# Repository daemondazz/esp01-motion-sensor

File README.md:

# ESP-01 Based Motion Sensor

This project is a very simple motion sensor using an ESP-01 ESP8266 module and
HC-SR501/DSN-FIR800 motion sensor.

Countless other designs using the same ESP module and motion sensor exist, this
project was created as a learning exercise. And because I wanted to.

## PCB

The PCB folder contains a Kicad project for a simple PCB that both the ESP
module and motion sensor are mounted to. It has the following features:

* Allows direct mounting of the ESP-01 module
* Allows direct mounting of the HC-SR501 sensor as a daughter board
* Uses a micro-USB connector for power input
* Contains a 3.3V regulator for powering the ESP-01
* Includes required pull-up resistors to allow the ESP-01 to boot reliably and
  then use the GPIO2 pin for the sensor input

## Software

The Software folder contains the Arduino sketch that I am running on my modules. 
It has the following features:

* Automatically publishes state changes into an MQTT topic based on the Chip ID 
  number embedded in the ESP-01
* Automatically publishes a name/version/OTA state message into an MQTT topic
  based on the Chip ID embedded into the ESP-01 every 10s as a keepalive
* Supports password authenticated OTA updates for the first 2 minutes after 
  powering on or being reset
* Uses the TX LED as an activity indicator

## TODO

* Create a 3D printed case to house the PCB
* Allow creation of a command MQTT topic to issue commands

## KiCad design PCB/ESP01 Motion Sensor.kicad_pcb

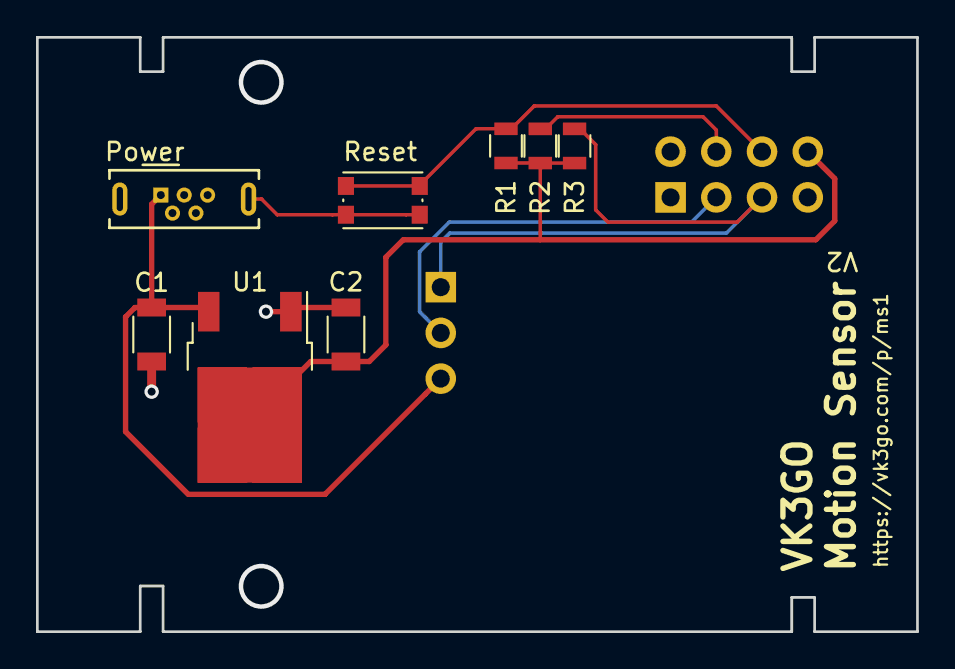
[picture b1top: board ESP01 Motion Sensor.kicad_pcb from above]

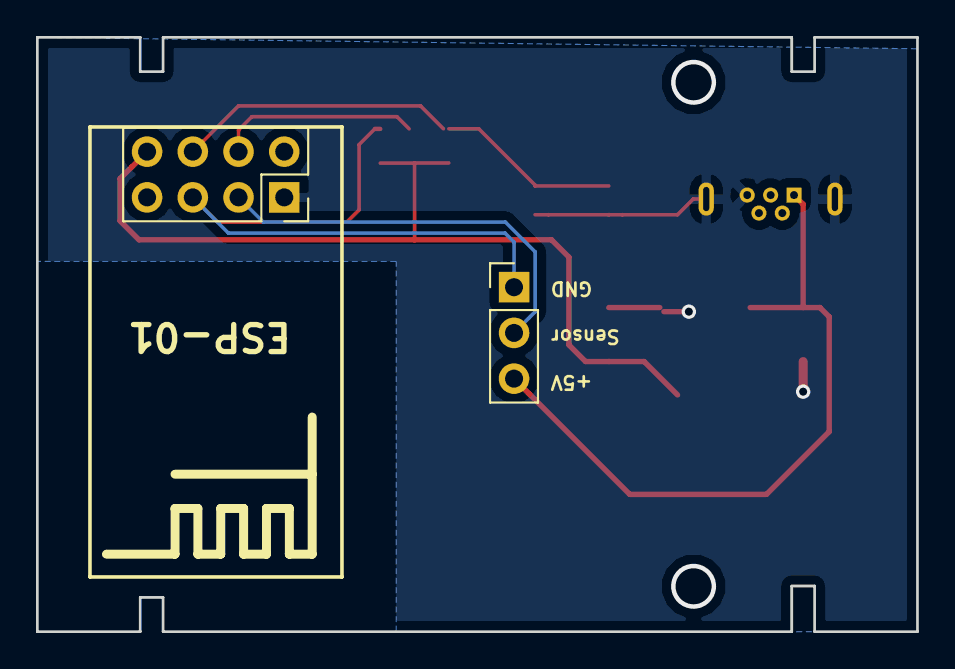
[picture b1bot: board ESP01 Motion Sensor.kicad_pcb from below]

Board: 2 copper layers, 48.9 x 33.0 mm, 10 parts (2 on the bottom side), 7 nets.

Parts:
C1, C2: 0.1uF; C_1206
J1: USB POWER; USB_Micro-B_Wuerth-614105150721_Vertical
J2: Conn_01x03_Female; Socket_Strip_Straight_1x03_Pitch2.54mm
R1, R2, R3: 10K; R_0805
SW1: SW_Push; SW_SPST_KMR2
U1: NCP1117-3.3; TO-252-2
U2: ESP-01; Socket_Strip_Straight_2x04_Pitch2.54mm

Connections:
+3V3: C2.1, R1.2, R2.2, R3.2, U1.2, U2.8
+5V: C1.1, J1.1, J2.3, U1.3
/CH_PD: R2.1, U2.4
/GPIO0: J2.1, R3.1, U2.5
/GPIO2: J2.2, U2.3
/RST: R1.1, SW1.1, U2.6
GND: C1.2, C2.2, J1.5, J1.6, SW1.2, U1.1, U2.1

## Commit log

2018-01-11 Add readme.md
2018-01-11 Add initial schematic and PCB layout
2018-01-11 Add initial gerber plots
2018-01-12 Add initial arduino-ide code for running microcontroller
2018-01-12 Add gitlab-ci script to mirror repository from our internal GitLab to public GitHub. Ensure GITHUB_USER and GITHUB_PASS are set in project CI settings as secret. Use samueldebruyn/debian-git image as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
2018-01-12 Force a pull before pushing to ensure we have latest commit
2018-01-12 Oops, specify remote and branch
2018-01-12 Update README file and fix typos
2018-01-12 Update .gitlab-ci.yml with information from http://blog.plataformatec.com.br/2013/05/how-to-properly-mirror-a-git-repository/
2018-01-22 Fix pin numbering on ESP-01 header. Note to self: Always verify pin numbers!
2018-01-22 Fix ESP-01 pinout, rotate motion sensor module, make board 33x49mm, make mounting cutouts larger
